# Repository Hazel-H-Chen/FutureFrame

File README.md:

# Future Frame LightCore

Future Frame LightCore is a high precision illumination system designed for photographic film scanning. The device provides controlled multi channel lighting to ensure accurate color reproduction, uniform illumination, and additional imaging capabilities such as infrared dust detection.

## Overview

LightCore generates stable, controllable illumination using five independent light channels: red, green, blue, white, and infrared. The system allows precise control of light intensity and color balance, making it suitable for high quality digitization of photographic film.

A custom PCB and microcontroller system manage power delivery, LED current control, and system monitoring. 

## Hardware Architecture

The system is controlled by a Seeed Studio XIAO microcontroller mounted on a custom PCB. Power is delivered through a two stage regulation system that converts a high voltage input to stable low voltage rails for the electronics.

Key hardware components include:

* Seeed Studio XIAO microcontroller
* Four AL8860WT LED drivers
* Four channel DAC for current control
* MOSFET driver circuit for the infrared channel
* Temperature sensor for thermal monitoring

The LED drivers provide independent current control for the RGBW channels, while the infrared channel is used for dust detection and infrared transmission during scanning. 

## Power System

The board uses a two stage power conversion architecture:

* Buck converter: 36V to 5V
* LDO regulator: 5V to 3.3V

This configuration allows efficient power delivery while maintaining stable logic and control voltages. 

## Mechanical Design

The light source is mounted inside a custom enclosure consisting of:

* 3D printed structural housing
* Sheet aluminum side panels for rigidity
* Waterjet aluminum heat dissipator for thermal management
* Two stage diffusion system for uniform backlighting

A secondary control PCB inside the enclosure includes a rotary encoder, switches, and an OLED display for user interaction. 

## Features

* Five channel LED illumination system (RGB, white, infrared)
* High precision current control
* Active temperature monitoring
* Uniform diffused backlighting
* Integrated user control interface

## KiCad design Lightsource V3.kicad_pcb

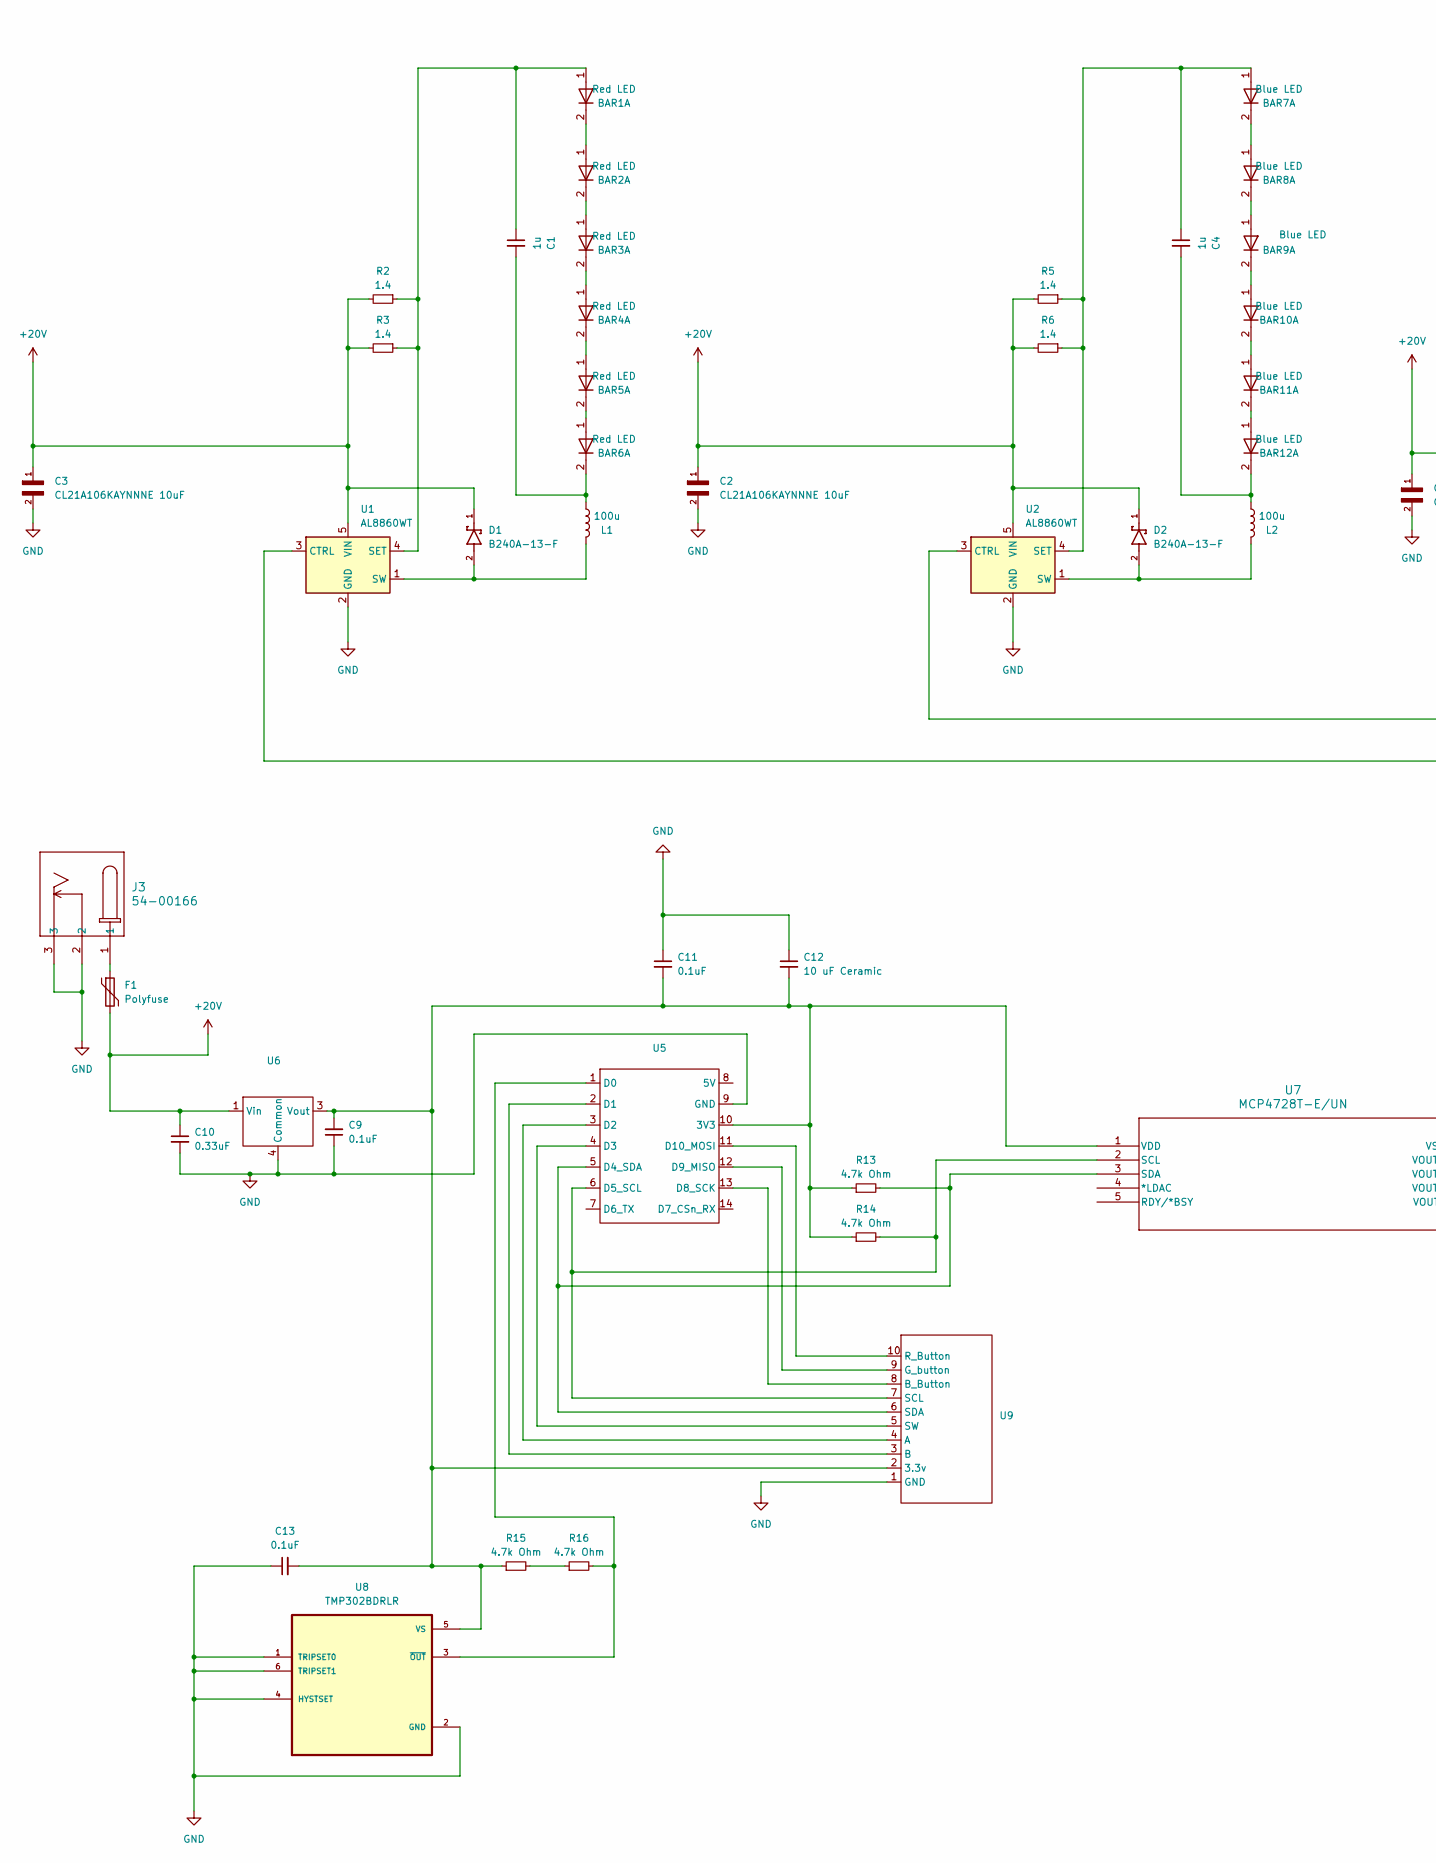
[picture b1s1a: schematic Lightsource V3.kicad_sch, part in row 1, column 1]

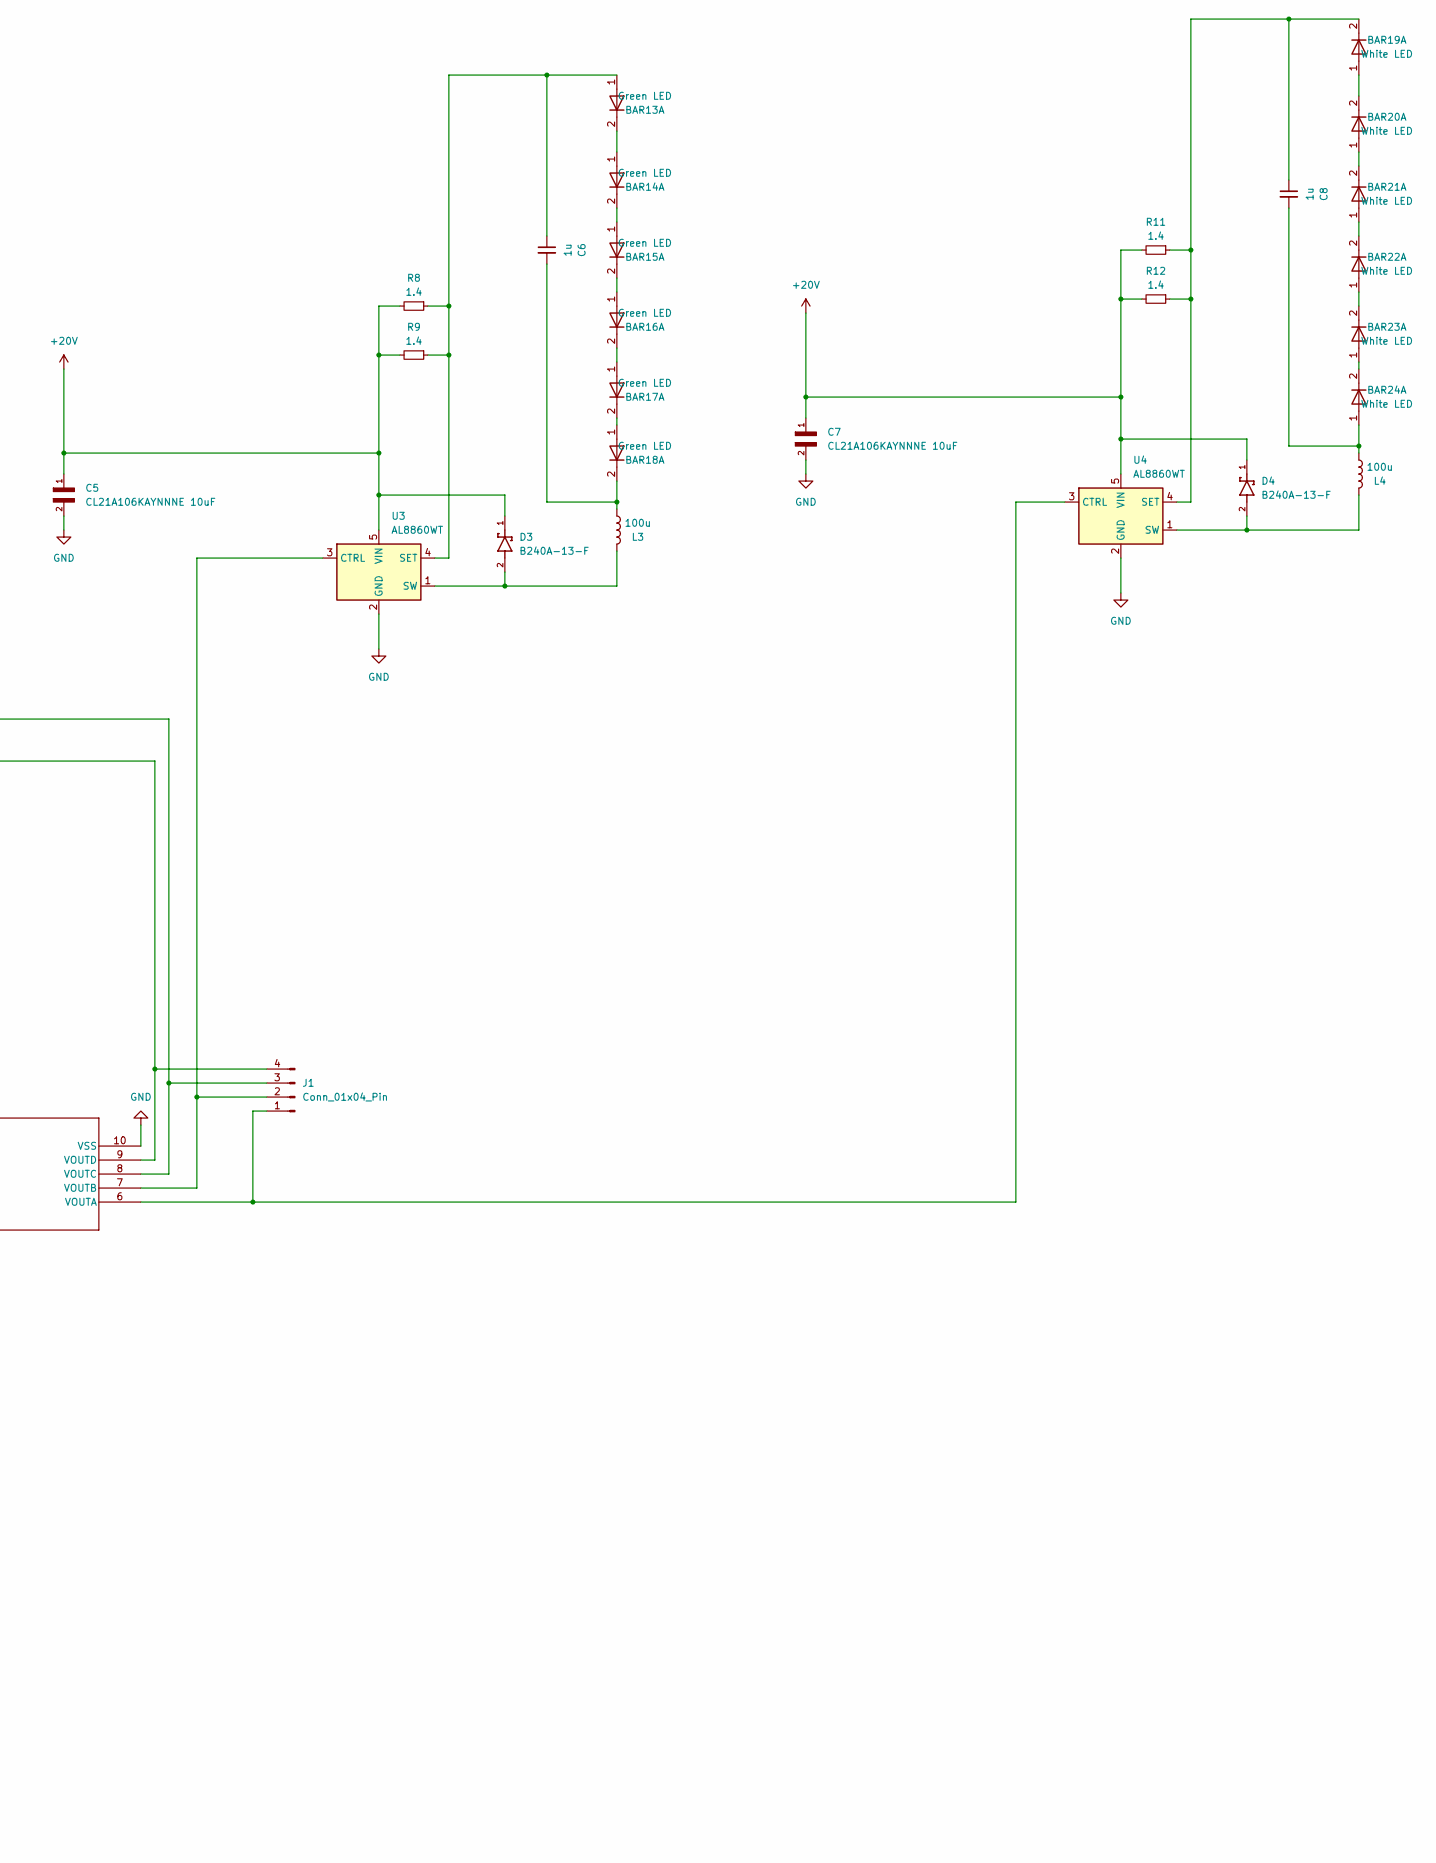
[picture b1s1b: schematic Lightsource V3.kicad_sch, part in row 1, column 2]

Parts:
BAR1, BAR2, BAR3, BAR4, BAR5, BAR6: Red LED; LED_PLCC_2835
BAR7, BAR8, BAR9, BAR10, BAR11, BAR12: Blue LED; LED_PLCC_2835
BAR13, BAR14, BAR15, BAR16, BAR17, BAR18: Green LED; LED_PLCC_2835
BAR19, BAR20, BAR21, BAR22, BAR23, BAR24: White LED; LED_PLCC_2835
C1, C4, C6, C8: 1u; C_0805_2012Metric
C2, C3, C5, C7: CL21A106KAYNNNE 10uF; C_0805_2012Metric
C9, C11, C13: 0.1uF; C_0805_2012Metric
C10: 0.33uF; C_0805_2012Metric
C12: 10 uF Ceramic; C_0805_2012Metric
D1, D2, D3, D4: B240A-13-F; D_SMA; PARTREV 22 - 2
F1: Polyfuse; C_1812_4532Metric
J1: Conn_01x04_Pin; PinHeader_1x04_P2.54mm_Vertical
J3: 54-00166; CUI_PJ-202A
L1, L2, L3, L4: 100u; C_1210_3225Metric
R2, R3, R5, R6, R8, R9, R11, R12: 1.4; R_0805_2012Metric
R13, R14, R15, R16: 4.7k Ohm; R_0805_2012Metric
U1, U2, U3, U4: AL8860WT; TSOT-23-5
U5: 2.54mm 7pin Female Header_1
U6: UA78M33CKVURG3
U7: MCP4728T-E/UN; MSOP10_MC_MCH
U8: TMP302BDRLR; SOT50P160X60-6N
U9: PinHeader_1x10_P2.54mm_Vertical

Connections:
+20V: C2.1, C3.1, C5.1, C7.1, C10.1, D1.1, D2.1, D3.1, D4.1, F1.2, R2.2, R3.2, R5.2, R6.2, R8.2, R9.2, R11.2, R12.2, U1.5 (VIN), U2.5 (VIN), U3.5 (VIN), U4.5 (VIN), U6.1 (Vin)
GND: C2.2, C3.2, C5.2, C7.2, C9.1, C10.2, C11.1, C12.1, C13.1, J3.2, J3.3, U1.2 (GND), U2.2 (GND), U3.2 (GND), U4.2 (GND), U5.9 (GND), U6.4 (Common), U7.10 (VSS), U8.1 (TRIPSET0), U8.2 (GND), U8.4 (HYSTSET), U8.6 (TRIPSET1), U9.1 (GND)
unnamed: BAR1.1 (A), C1.1, R2.1, R3.1, U1.4 (SET)
unnamed: BAR1.2 (K), BAR2.1 (A)
unnamed: BAR2.2 (K), BAR3.1 (A)
unnamed: BAR3.2 (K), BAR4.1 (A)
unnamed: BAR4.2 (K), BAR5.1 (A)
unnamed: BAR5.2 (K), BAR6.1 (A)
unnamed: BAR6.2 (K), C1.2, L1.1
unnamed: BAR7.1 (A), C4.1, R5.1, R6.1, U2.4 (SET)
unnamed: BAR7.2 (K), BAR8.1 (A)
unnamed: BAR8.2 (K), BAR9.1 (A)
unnamed: BAR9.2 (K), BAR10.1 (A)
unnamed: BAR10.2 (K), BAR11.1 (A)
unnamed: BAR11.2 (K), BAR12.1 (A)
unnamed: BAR12.2 (K), C4.2, L2.1
unnamed: BAR13.1 (A), C6.1, R8.1, R9.1, U3.4 (SET)
unnamed: BAR13.2 (K), BAR14.1 (A)
unnamed: BAR14.2 (K), BAR15.1 (A)
unnamed: BAR15.2 (K), BAR16.1 (A)
unnamed: BAR16.2 (K), BAR17.1 (A)
unnamed: BAR17.2 (K), BAR18.1 (A)
unnamed: BAR18.2 (K), C6.2, L3.1
unnamed: BAR19.1 (A), BAR20.2 (K)
unnamed: BAR19.2 (K), C8.1, R11.1, R12.1, U4.4 (SET)
unnamed: BAR20.1 (A), BAR21.2 (K)
unnamed: BAR21.1 (A), BAR22.2 (K)
unnamed: BAR22.1 (A), BAR23.2 (K)
unnamed: BAR23.1 (A), BAR24.2 (K)
unnamed: BAR24.1 (A), C8.2, L4.1
unnamed: F1.1, J3.1
unnamed: J1.1, U4.3 (CTRL), U7.6 (VOUTA)
unnamed: J1.2, U3.3 (CTRL), U7.7 (VOUTB)
unnamed: J1.3, U2.3 (CTRL), U7.8 (VOUTC)
unnamed: J1.4, U1.3 (CTRL), U7.9 (VOUTD)
unnamed: R15.2, R16.1
unnamed: D1.2, L1.2, U1.1 (SW)
unnamed: D2.2, L2.2, U2.1 (SW)
unnamed: D3.2, L3.2, U3.1 (SW)
unnamed: D4.2, L4.2, U4.1 (SW)
unnamed: C9.2, C11.2, C12.2, C13.2, R13.1, R14.1, R15.1, U5.10 (3V3), U6.3 (Vout), U7.1 (VDD), U8.5 (VS), U9.2 (3.3v)
unnamed: R16.2, U5.1 (D0), U8.3 (~OUT)
unnamed: U5.2 (D1), U9.3 (B)
unnamed: U5.3 (D2), U9.4 (A)
unnamed: U5.4 (D3), U9.5 (SW)
unnamed: R13.2, U5.5 (D4_SDA), U7.3 (SDA), U9.6 (SDA)
unnamed: R14.2, U5.6 (D5_SCL), U7.2 (SCL), U9.7 (SCL)
unnamed: U5.13 (D8_SCK), U9.8 (B_Button)
unnamed: U5.12 (D9_MISO), U9.9 (G_button)
unnamed: U5.11 (D10_MOSI), U9.10 (R_Button)

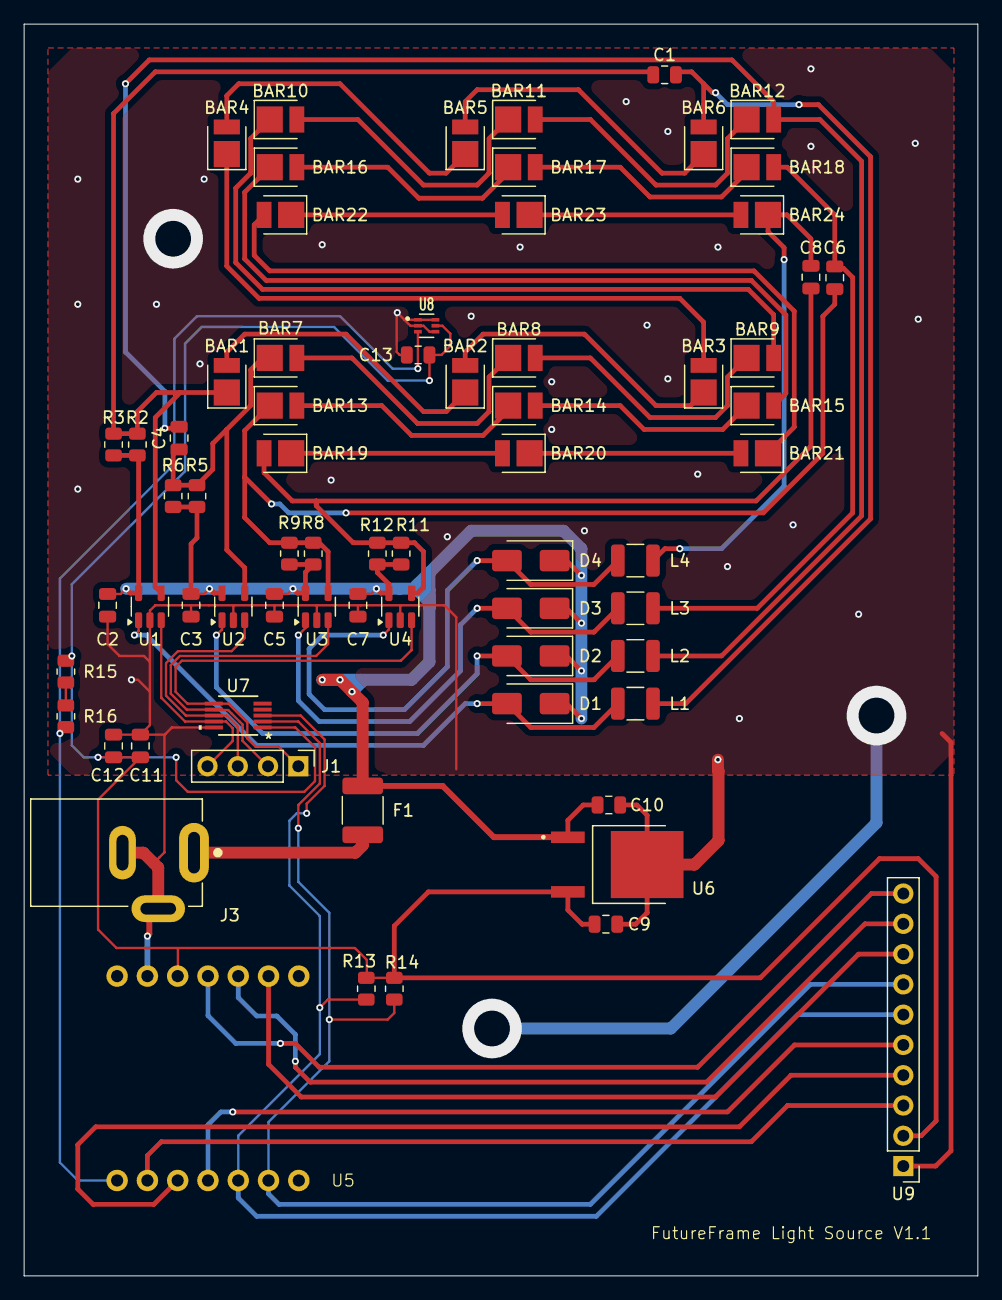
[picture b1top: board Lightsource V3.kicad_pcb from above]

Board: 2 copper layers, 80.0 x 105.0 mm, 69 parts (0 on the bottom side), 50 nets.

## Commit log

2026-03-18 Rename Lightsource V3.kicad_pcb to d
2026-03-18 Rename Lightsource V3.kicad_pcb to pcb/Lightsource V3.kicad_pcb
2026-03-18 Rename Lightsource V3.kicad_pro to pcb/Lightsource V3.kicad_pro
2026-03-18 Rename Lightsource V3.kicad_sch to pcb/Lightsource V3.kicad_sch
2026-03-18 Rename ibom.html to pcb/ibom.html
